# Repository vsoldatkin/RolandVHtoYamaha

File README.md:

Roland VH to Yamaha adapter
================

This KiCad project represents a simple adapter which allows you to connect Roland Virtual Hi-Hat controllers (like VH-11, VH-12, VH-13) to Yamaha drum modules (DTX series).

## Tested configurations:

|         |DTX Multi 12|DTX 400|DTX 500|DTX 700|DTX 900|
|---------|:----------:|:-----:|:-----:|:-----:|:-----:|
|**VH-11**|            |       |       |       |       |
|**VH-12**|            |       |       |       |       |
|**VH-13**|      OK    |       |       |       |       |

Note: I haven't produced a PCB which is included here yet. So I can't say if it is OK for production.

## Operation principles

This adapter emulates Yamaha HH65 Hi-hat controller. So it should probably work with every drum module that accepts HH65.

HH65 sequentially connects drum modules's input to the ground via the set of resistances depending on the pressure:

1. Pedal is depressed: module's input floats
2. Pressure level 1: 100k between ground and input
3. Pressure level 2: 100k + 47k in parallel
4. Pressure level 3: 100k + 47k + 10k in parallel
5. Pedal is fully pressed: input is shorted to ground

Drum module supplies power to the scheme via the TIP terminal. It appears that the supplied voltage varies depending on the module. Adapter should work with both +3.3V and +5V power levels.

## Tuning
Adapter was designed to be flexible. Four potentiometers RV1, RV2, RV3, RV4 adjust reference voltage levels which allows the comparator to gradually connect R3, R4, R5 and finally short the module's input to ground.

To tune the adapter one simply need to adjust the potentiometers so the voltage levels on a debug pins are like this: V5 > V4 > V3 > V2 > V1 > V5low. Where V5 is the voltage on the pin P5 when the hi-hat controller is fully depressed, and V5low is the voltage on P5 when the controller is fully pressed. Each interval (e.g. between V5 and V4, V4 and V3, etc.) should be roughly the same. In most cases this should be enough. 

It is possible to adjust reference voltages in a different proportions to get other response curves.

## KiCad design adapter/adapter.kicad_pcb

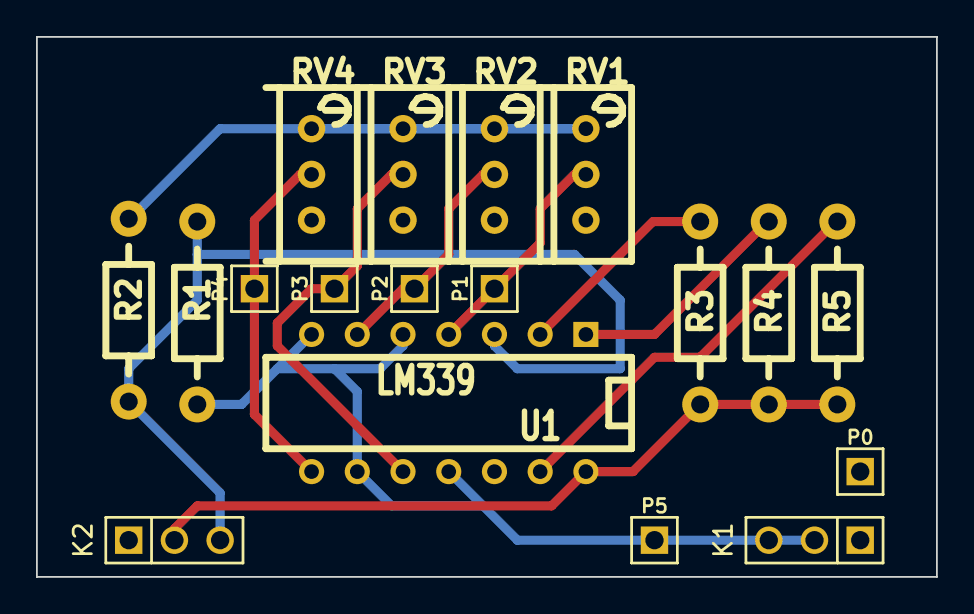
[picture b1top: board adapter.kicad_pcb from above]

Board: 2 copper layers, 50.0 x 30.0 mm, 18 parts (0 on the bottom side), 12 nets.

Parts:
K1: To VHH; pin_array_1x03
K2: To DTX; pin_array_1x03
P0, P1, P2, P3, P4, P5: pin_array_1x01
R1, R2: 100k; Resistor_Horizontal_RM10mm
R3: 150k; Resistor_Horizontal_RM10mm
R4: 47k; Resistor_Horizontal_RM10mm
R5: 10k; Resistor_Horizontal_RM10mm
RV1, RV2, RV3, RV4: 100k; Potentiometer_Bourns_3296W_3-8Zoll_Inline_ScrewUp
U1: LM339; DIP-14__300

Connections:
+3.3V: K2.3, R1.1, R2.1, U1.3
GND: K1.1, K2.1, P0.1, RV1.3, RV2.3, RV3.3, RV4.3, U1.12
unnamed: K1.2, K1.3, P5.1, R1.2, U1.5, U1.7, U1.9, U1.11
unnamed: K2.2, R3.2, R4.2, R5.2, U1.14
unnamed: P1.1, RV1.2, U1.4
unnamed: P2.1, RV2.2, U1.6
unnamed: P3.1, RV3.2, U1.10
unnamed: P4.1, RV4.2, U1.8
unnamed: R2.2, RV1.1, RV2.1, RV3.1, RV4.1
unnamed: R3.1, U1.2
unnamed: R4.1, U1.1
unnamed: R5.1, U1.13

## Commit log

2014-05-11 Initial schematics
2014-05-11 Minor README.md fixes
2014-05-13 Minor README.md fix
